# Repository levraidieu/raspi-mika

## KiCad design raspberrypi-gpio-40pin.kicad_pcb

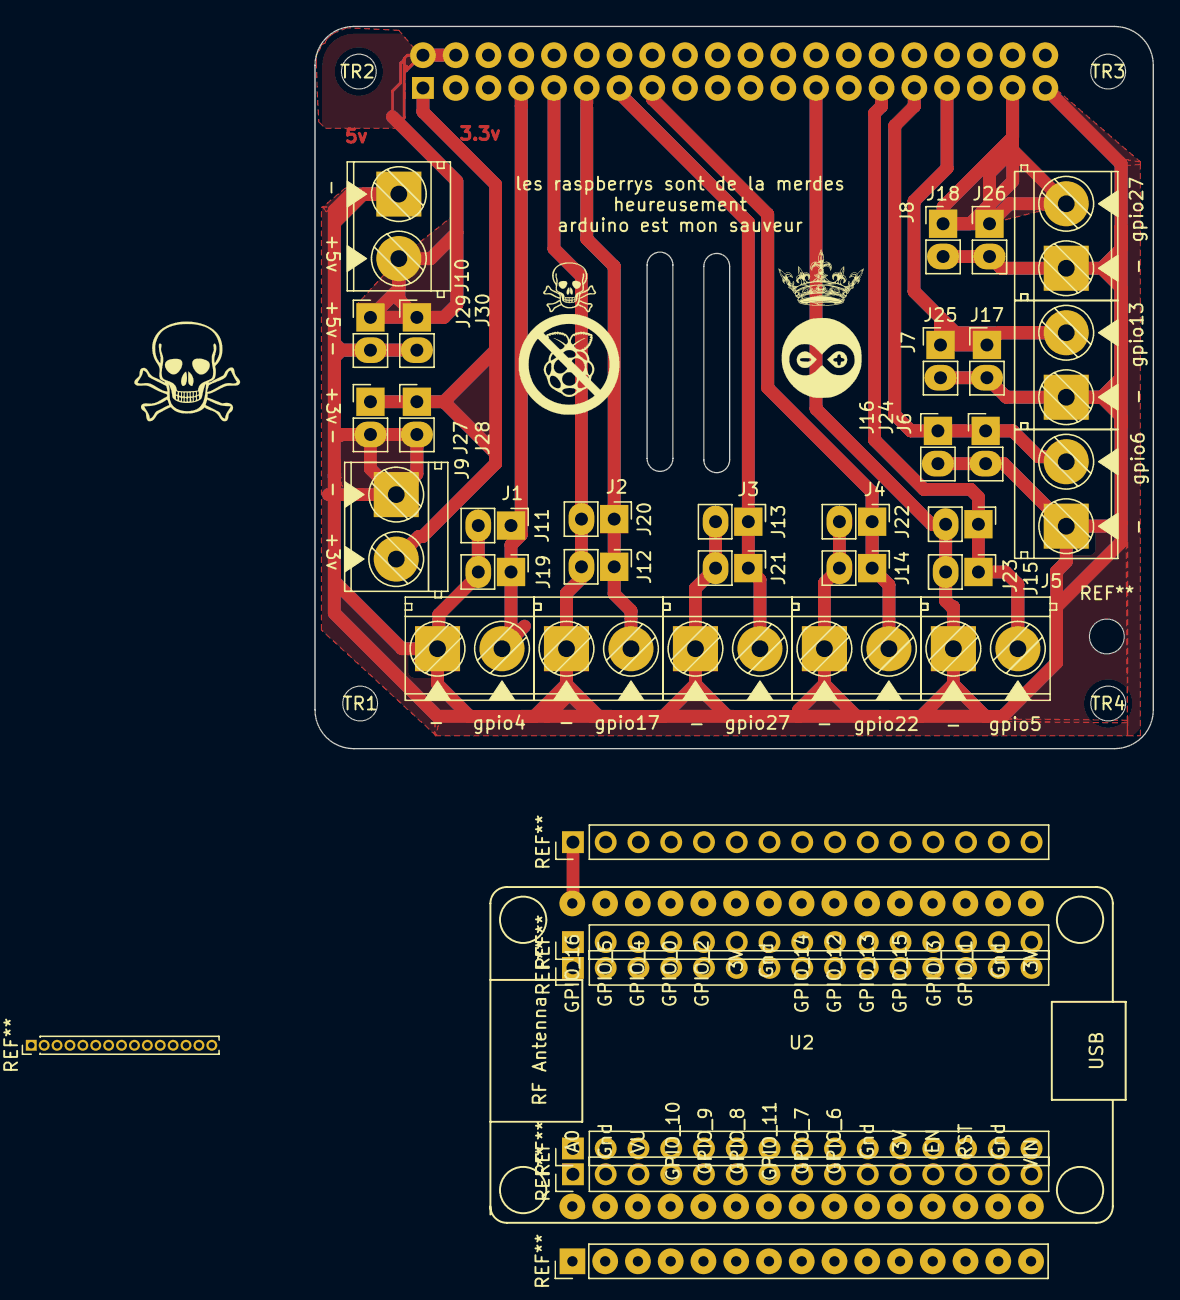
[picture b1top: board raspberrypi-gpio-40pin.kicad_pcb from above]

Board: 2 copper layers, 65.0 x 56.0 mm, 36 parts (1 on the bottom side), 11 nets.

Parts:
J1, J2, J3, J4, J5, J6, J7, J8, J9, J10: Conn_01x02_Female; bornier_2pts_L10mm_W8mm
J11, J12, J13, J14, J15, J16, J17, J18, J19, J20, J21, J22, J23, J24, J25, J26, J27, J28, J29, J30: Conn_01x02_Male; PinHeader_1x02_P2.54mm_Vertical
P1: Conn_02x20_Odd_Even; Socket_Strip_Straight_2x20_Pitch2.54mm
TR1, TR2, TR3, TR4: MountingHole_2.7mm_M2.5
U2: ESP8266EX-NODEMCU-FRED-chaudier; ESP12F-Devkit-V3-fred-GPIO-1

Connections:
+3V3: J9.2, J27.1, J28.1, P1.1, P1.17
+5V: J10.2, J29.1, J30.1, P1.2, P1.4
/GPIO4(GCLK): J1.2, J11.1, J19.1, P1.7
/GPIO5: J5.2, J15.1, J23.1, P1.29
/GPIO6: J6.2, J16.1, J24.1, P1.31
/GPIO13(PWM1): J7.2, J17.1, J25.1, P1.33
/GPIO17(GEN0): J2.2, J12.1, J20.1, P1.11
/GPIO22(GEN3): J4.2, J14.1, J22.1, P1.15
/GPIO26: J8.2, J18.1, J26.1, P1.37
/GPIO27(GEN2): J3.2, J13.1, J21.1, P1.13
GND: J1.1, J2.1, J3.1, J4.1, J5.1, J6.1, J7.1, J8.1, J9.1, J10.1, J11.2, J12.2, J13.2, J14.2, J15.2, J16.2, J17.2, J18.2, J19.2, J20.2, J21.2, J22.2, J23.2, J24.2, J25.2, J26.2, J27.2, J28.2, J29.2, J30.2, P1.6, P1.9, P1.14, P1.20, P1.25, P1.30, P1.34, P1.39

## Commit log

2019-12-02 debut
2019-12-02 mise a jour
    dgf
2019-12-03 mika
2019-12-03 masse
2019-12-03 mise a jour
2019-12-03 ghgf
2019-12-03 ffhg
2019-12-03 dcsd
2019-12-04 logo
2019-12-04 Update raspberrypi-gpio-40pin.kicad_pcb-bak
2019-12-04 tfyfg
2019-12-04 hgfy
2019-12-04 utfuft
2019-12-04 ytfyf
2019-12-05 quasi final
2019-12-07 couronne
2019-12-17 logo raspi
2019-12-17 khkhk
2020-01-08 mie a jour esp8266
